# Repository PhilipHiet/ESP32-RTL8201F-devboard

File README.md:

# ESP32-RTL8201F-devboard
A simple ESP32 devboard with WiFi and Ethernet using the RTL8201F transceiver including an onboard USB-C-port for power, programming and serial console.

## Design

The schematics are based on the [esp-32-poe-dev project by @jorticus](https://github.com/jorticus/esp32-poe-dev) but using the ESP32-WROOM-32E module instead of a barebone ESP32.

This board is designed as a 4-layer PCB and is optimized for cheap assembly with JLCPCB. So using basic parts where possible and a custom ESP32-WROOM-32E footrpint so the minimum via-hole-size is 0.3mm.

## Assembly

The boards were fully assembled by JLCPCB (except for the pinheaders).
The necessary production files are included under pcb/jilcpcb.

In the first interation I chose the wrong 3.3V LDO and had to amnually swap those. The uploaded board- and assembly-files are already fixed.

## Development using platform.io
Save the [esp32-rtl8201f-devboard.json](esp32-rtl8201f-devboard.json) into the `boards` directory of your platform.io project. Creating the folder if it doesn't exist yet.

Select the board in your `platformio.ini`
```ini
[env:esp32dev]
monitor_speed=115200
platform = espressif32
board = esp32-rtl8201f-devboard
framework = arduino
```
Now you can `#include <ETH.h>` and call `ETH.begin();` in your code.
Check out the [firmware-examples](firmware-examples) for more details.

## Stability
The main goal was to have a more stable link than the onboard wifi and with packet-loss around .00003% in my test I think it's pretty stable.

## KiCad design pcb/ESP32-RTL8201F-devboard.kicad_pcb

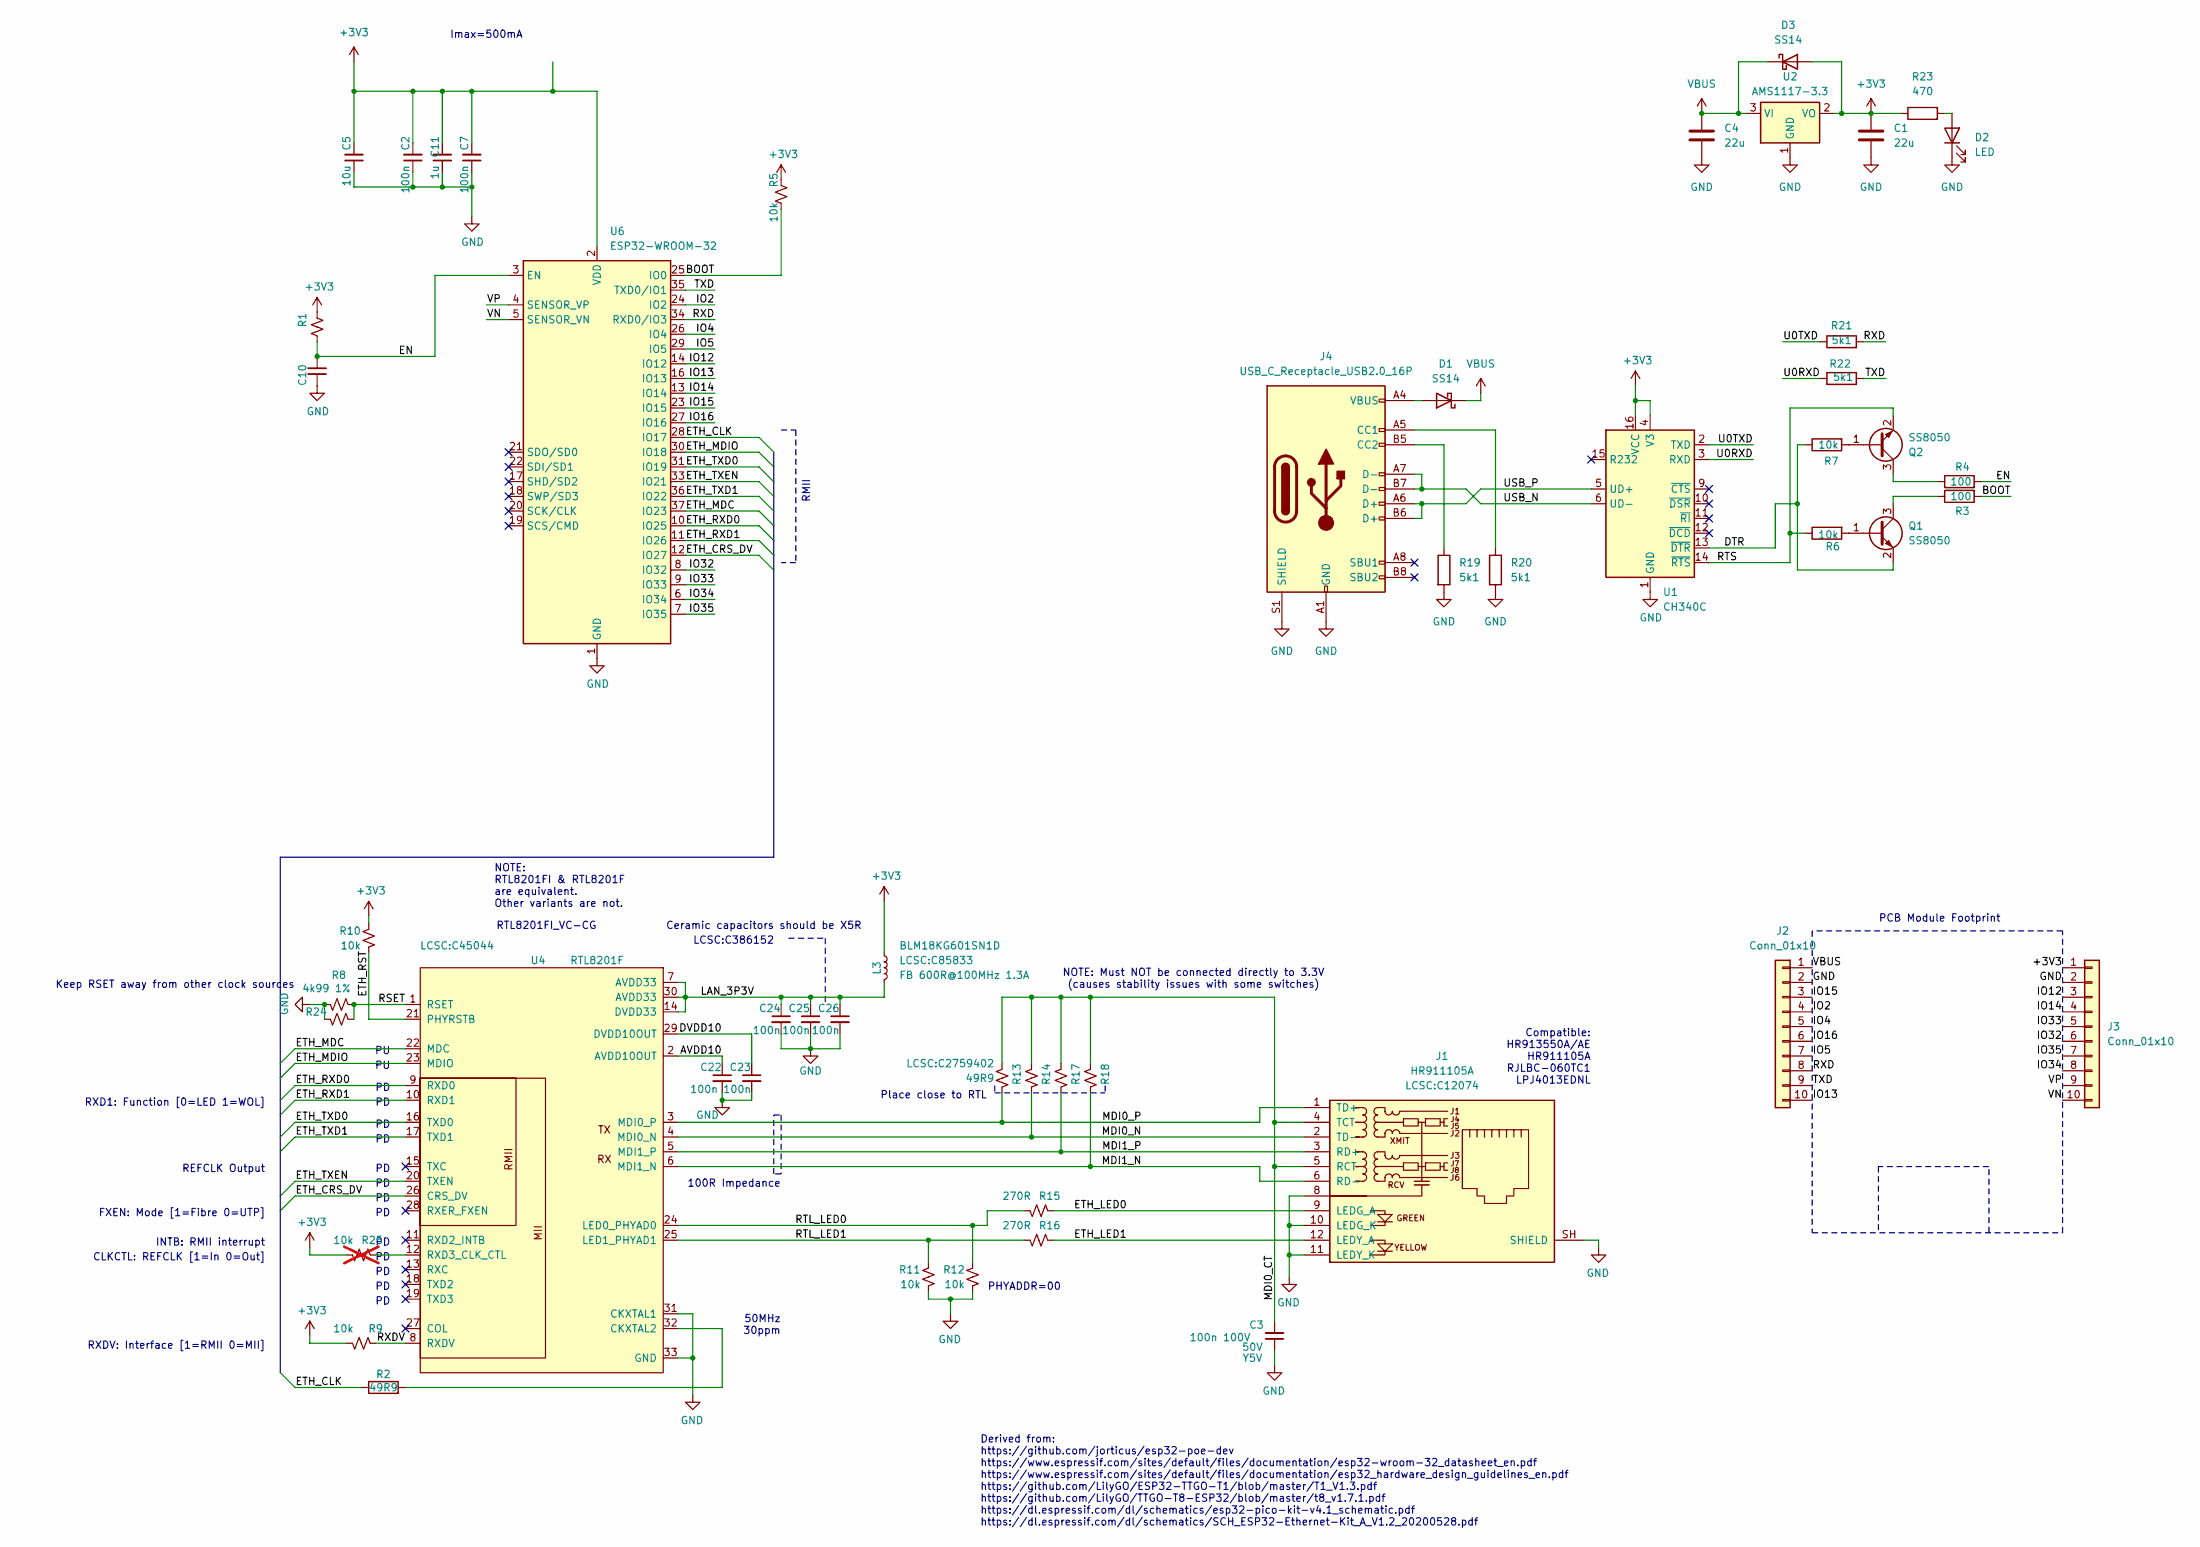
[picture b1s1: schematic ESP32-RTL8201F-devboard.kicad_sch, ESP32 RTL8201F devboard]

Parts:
C1, C4: 22u; C_0603_1608Metric; LCSC part number C59461
C2, C7, C22, C23, C24, C25, C26: 100n; C_0603_1608Metric; LCSC part number C14663
C3: 100n 100V; C_0603_1608Metric; Rating 50V; LCSC part number C28233
C5: 10u; C_0603_1608Metric; LCSC part number C19702
C10, C11: 1u; C_0603_1608Metric; LCSC part number C15849
D1, D3: SS14; D_SMA; LCSC part number C2480
D2: LED; LED_0603_1608Metric; LCSC part number C2286
J1: HR911105A; RJ45_Hanrun_HR911105A_Horizontal; Part LCSC:C12074; LCSC part number C12074
J2, J3: Conn_01x10; PinHeader_1x10_P2.54mm_Vertical
J4: USB_C_Receptacle_USB2.0_16P; USB_C_Receptacle_G-Switch_GT-USB-7010ASV; LCSC part number C393939
L3: FB 600R@100MHz 1.3A; L_0603_1608Metric; Part1 LCSC:C85833; LCSC part number C85833
Q1, Q2: SS8050; SOT-23; LCSC part number C2150
R1, R5, R6, R7, R9, R10, R11, R12: 10k; R_0603_1608Metric; LCSC part number C25804
R2: 49R9; R_0603_1608Metric; LCSC part number C23185
R3, R4: 100; R_0603_1608Metric; LCSC part number C22775
R8, R24: 4k99 1%; R_0603_1608Metric; LCSC part number C23046
R13: 49R9; R_0603_1608Metric; Part LCSC:C2759402; LCSC part number C23185
R14, R17, R18: 49.9R 1%; R_0603_1608Metric; LCSC part number C23185
R15, R16: 270R; R_0603_1608Metric; LCSC part number C22966
R19, R20, R21, R22: 5k1; R_0603_1608Metric; LCSC part number C23186
R23: 470; R_0603_1608Metric; LCSC part number C23179
R25: 10k; R_0603_1608Metric; LCSC part number C25804; not fitted
U1: CH340C; SOIC-16_3.9x9.9mm_P1.27mm; LCSC part number C84681
U2: AMS1117-3.3; SOT-223-3_TabPin2; LCSC part number C6186
U4: RTL8201F; QFN-32-1EP_5x5mm_P0.5mm_EP3.1x3.1mm; Part2 LCSC:C45044; LCSC part number C45044
U6: ESP32-WROOM-32; ESP32-WROOM-32E; LCSC part number C701342

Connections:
+3V3: C1.1, C2.2, C5.2, C7.2, C11.2, D3.2 (A), J3.1, L3.1, R1.2, R5.2, R9.1, R10.1, R23.1, R25.1, U1.4 (V3), U1.16 (VCC), U2.2 (VO), U6.2 (VDD)
/AVDD10: C22.1, U4.2 (AVDD10OUT)
/BOOT: R3.2, R5.1, U6.25 (IO0)
/DTR: Q1.2 (E), R7.1, U1.13 (~DTR)
/DVDD10: C23.1, U4.29 (DVDD10OUT)
/EN: C10.2, R1.1, R4.2, U6.3 (EN)
/ETH_CLK: R2.1, U6.28 (IO17)
/ETH_CRS_DV: U4.26 (CRS_DV), U6.12 (IO27)
/ETH_LED0: J1.9 (LEDG_A), R15.2
/ETH_LED1: J1.12 (LEDY_A), R16.2
/ETH_MDC: U4.22 (MDC), U6.37 (IO23)
/ETH_MDIO: U4.23 (MDIO), U6.30 (IO18)
/ETH_RST: R10.2, U4.21 (PHYRSTB)
/ETH_RXD0: U4.9 (RXD0), U6.10 (IO25)
/ETH_RXD1: U4.10 (RXD1), U6.11 (IO26)
/ETH_TXD0: U4.16 (TXD0), U6.31 (IO19)
/ETH_TXD1: U4.17 (TXD1), U6.36 (IO22)
/ETH_TXEN: U4.20 (TXEN), U6.33 (IO21)
/IO2: J2.4, U6.24 (IO2)
/IO4: J2.5, U6.26 (IO4)
/IO5: J2.7, U6.29 (IO5)
/IO12: J3.3, U6.14 (IO12)
/IO13: J2.10, U6.16 (IO13)
/IO14: J3.4, U6.13 (IO14)
/IO15: J2.3, U6.23 (IO15)
/IO16: J2.6, U6.27 (IO16)
/IO32: J3.6, U6.8 (IO32)
/IO33: J3.5, U6.9 (IO33)
/IO34: J3.8, U6.6 (IO34)
/IO35: J3.7, U6.7 (IO35)
/LAN_3P3V: C24.1, C25.1, C26.1, L3.2, U4.7 (AVDD33), U4.14 (DVDD33), U4.30 (AVDD33)
/MDI0_CT: C3.2, J1.4 (TCT), J1.5 (RCT), R13.1, R14.1, R17.1, R18.1
/MDI0_N: J1.2 (TD-), R14.2, U4.4 (MDI0_N)
/MDI0_P: J1.1 (TD+), R13.2, U4.3 (MDI0_P)
/MDI1_N: J1.6 (RD-), R18.2, U4.6 (MDI1_N)
/MDI1_P: J1.3 (RD+), R17.2, U4.5 (MDI1_P)
/RSET: R8.2, R24.2, U4.1 (RSET)
/RTL_LED0: R12.1, R15.1, U4.24 (LED0_PHYAD0)
/RTL_LED1: R11.1, R16.1, U4.25 (LED1_PHYAD1)
/RTS: Q2.2 (E), R6.1, U1.14 (~RTS)
/RXD: J2.8, R21.2, U6.34 (RXD0/IO3)
/RXDV: R9.2, U4.8 (RXDV)
/TXD: J2.9, R22.2, U6.35 (TXD0/IO1)
/U0RXD: R22.1, U1.3 (RXD)
/U0TXD: R21.1, U1.2 (TXD)
/USB_N: J4.A7 (D-), J4.B7 (D-), U1.6 (UD-)
/USB_P: J4.A6 (D+), J4.B6 (D+), U1.5 (UD+)
/VN: J3.10, U6.5 (SENSOR_VN)
/VP: J3.9, U6.4 (SENSOR_VP)
GND: C1.2, C2.1, C3.1, C4.2, C5.1, C7.1, C10.1, C11.1, C22.2, C23.2, C24.2, C25.2, C26.2, D2.1 (K), J1.8, J1.10 (LEDG_K), J1.11 (LEDY_K), J1.SH (SHIELD), J2.2, J3.2, J4.A1 (GND), J4.A12 (GND), J4.B1 (GND), J4.B12 (GND), J4.S1 (SHIELD), R8.1, R11.2, R12.2, R19.2, R20.2, R24.1, U1.1 (GND), U2.1 (GND), U4.31 (CKXTAL1), U4.33 (GND), U6.1 (GND), U6.15 (GND), U6.38 (GND), U6.39 (GND)
unnamed: D1.2 (A), J4.A4 (VBUS), J4.A9 (VBUS), J4.B4 (VBUS), J4.B9 (VBUS)
unnamed: D2.2 (A), R23.2
unnamed: J4.A5 (CC1), R20.1
unnamed: J4.B5 (CC2), R19.1
unnamed: Q1.1 (B), R6.2
unnamed: Q1.3 (C), R3.1
unnamed: Q2.1 (B), R7.2
unnamed: Q2.3 (C), R4.1
unnamed: R2.2, U4.32 (CKXTAL2)
unnamed: R25.2, U4.12 (RXD3_CLK_CTL)
VBUS: C4.1, D1.1 (K), D3.1 (K), J2.1, U2.3 (VI)

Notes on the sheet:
NOTE: Must NOT be connected directly to 3.3V (causes stability issues with some switches)
50MHz 30ppm
Keep RSET away from other clock sources
Derived from: https://github.com/jorticus/esp32-poe-dev https://www.espressif.com/sites/default/files/documentation/esp32-wroom-32_datasheet_en.pdf https://www.espressif.com/sites/default/files/documentation/esp32_hardware_design_guidelines_en.pdf https://github.com/LilyGO/ESP32-TTGO-T1/blob/master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
LCSC:C386152
Compatible: HR913550A/AE HR911105A RJLBC-060TC1 LPJ4013EDNL
Ceramic capacitors should be X5R
PCB Module Footprint
RXD1: Function [0=LED 1=WOL]
INTB: RMII interrupt
NOTE: RTL8201FI & RTL8201F are equivalent. Other variants are not.
RTL8201FI_VC-CG
PHYADDR=00
Imax=500mA
RXDV: Interface [1=RMII 0=MII]
REFCLK Output
100R Impedance
RMII
CLKCTL: REFCLK [1=In 0=Out]
FXEN: Mode [1=Fibre 0=UTP]
Place close to RTL

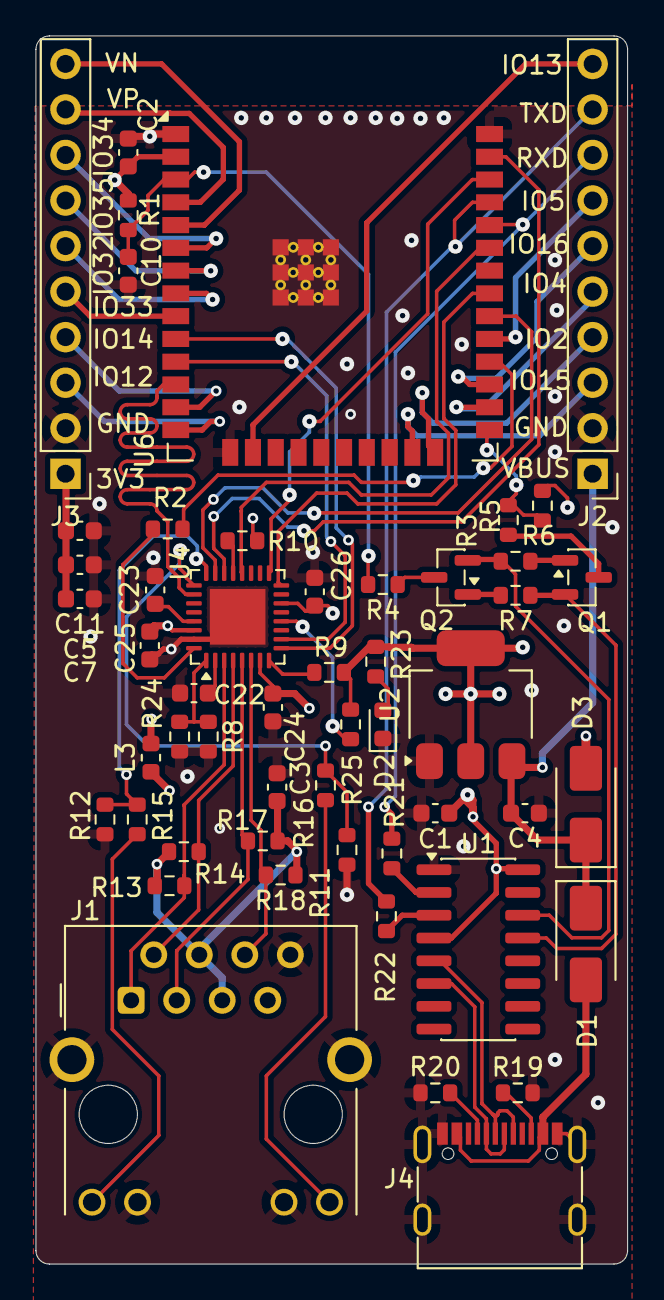
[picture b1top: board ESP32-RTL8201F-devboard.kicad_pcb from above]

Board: 4 copper layers, 33.0 x 68.5 mm, 52 parts (0 on the bottom side), 61 nets.

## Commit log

2026-04-20 Add MIT License
2026-04-20 Add IP-logger example
2026-04-20 Add license
2026-04-27 Board and doc
